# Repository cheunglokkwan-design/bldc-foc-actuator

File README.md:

# High-Precision Closed-Loop BLDC Actuator with Force-Feedback Control

This repository contains the design, simulation, firmware, and mechanical enclosure files for a high-performance, compact Brushless DC (BLDC) actuator. Designed on a NEMA 17 footprint, it integrates a 3-phase inverter power stage, absolute magnetic encoder feedback, and high-frequency Field Oriented Control (FOC) current-loop tuning for direct-drive robotic joints and haptic interfaces.

---

## Key Features

- **Field Oriented Control (FOC):** Smooth torque control using space vector modulation (SVPWM) and low-noise dual-shunt phase current sensing.
- **Embedded Electronics:** Compact 4-layer circular PCB (40mm diameter) combining power switching, current amplification, and STM32 microcontroller.
- **Parametric Mechanical Design:** Passive convection air cooling fins designed programmatically in OpenSCAD for lightweight 3D printing.
- **High-Frequency Control Loop:** Current sensing loop executes at 25 kHz inside high-priority interrupts to ensure instantaneous torque response.
- **Python Calibration GUI:** Serial telemetry dashboard to monitor speed, position, and tune PI control gains in real-time.

---

## Hardware Specifications

| Parameter | Value |
| :--- | :--- |
| **Input Supply Voltage** | 12V - 24V DC |
| **Continuous Current** | 15A (with passive cooling) |
| **Peak Current** | 30A (10-second thermal limit) |
| **Logic Voltage** | 3.3V (STM32 Internal LDO) |
| **Position Sensor** | AS5048A 14-bit Magnetic Encoder (SPI) |
| **Gate Driver** | DRV8305 with integrated Op-Amps |

---

## Directory Structure

- `/firmware`: Embedded C++ application for the STM32G474RET6 MCU.
- `/hardware`: KiCad 8.0 schematic and 4-layer layout files.
- `/mechanical`: OpenSCAD 3D design files and exported STL mounts.
- `/simulation`: LTspice switching transient circuit models and raw output data.
- `/gui`: Python monitoring dashboard.

---

## Getting Started

### 1. Build and Flash Firmware
The firmware utilizes the GCC ARM Toolchain and GNU Make.
```bash
cd firmware
make
# Flash target using STM32 CubeProgrammer or OpenOCD via ST-Link V3
openocd -f interface/stlink.cfg -f target/stm32g4x.cfg -c "program build/actuator_controller.bin verify reset exit"

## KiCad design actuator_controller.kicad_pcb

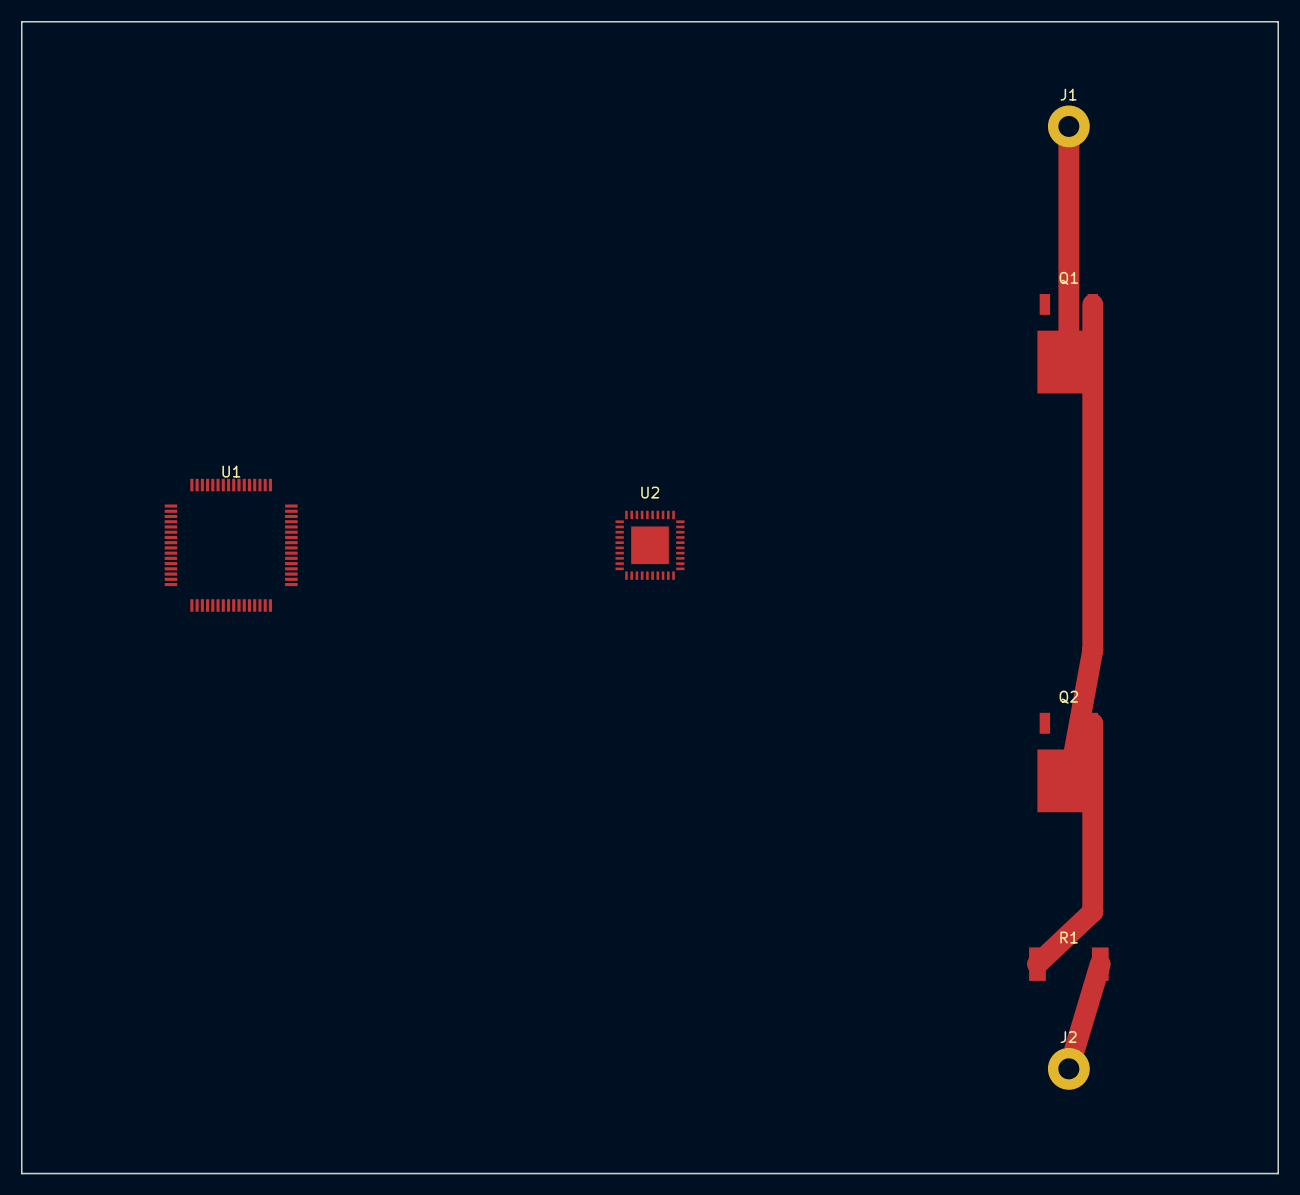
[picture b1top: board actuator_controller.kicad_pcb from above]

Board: 2 copper layers, 120.0 x 110.0 mm, 7 parts (0 on the bottom side), 4 nets.

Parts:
J1: +24V; SolderWirePad_1x01_Drill2mm
J2: GND; SolderWirePad_1x01_Drill2mm
Q1, Q2: CSD18532Q5B; TO-252-3_TabPin2
R1: 1m; R_2512_6332Metric
U1: STM32G474RET6; LQFP-64_10x10mm_P0.5mm
U2: DRV8305; QFN-40_6x6mm_P0.5mm

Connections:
+24V: J1.1, Q1.2
GND: J2.1, R1.2
PHASE_A: Q1.3, Q2.2
SHUNTP: Q2.3, R1.1

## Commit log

2026-06-09 README
2026-06-09 schematic
2026-06-09 Update KiCad Schematic File

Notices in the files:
README.md:
License: MIT
